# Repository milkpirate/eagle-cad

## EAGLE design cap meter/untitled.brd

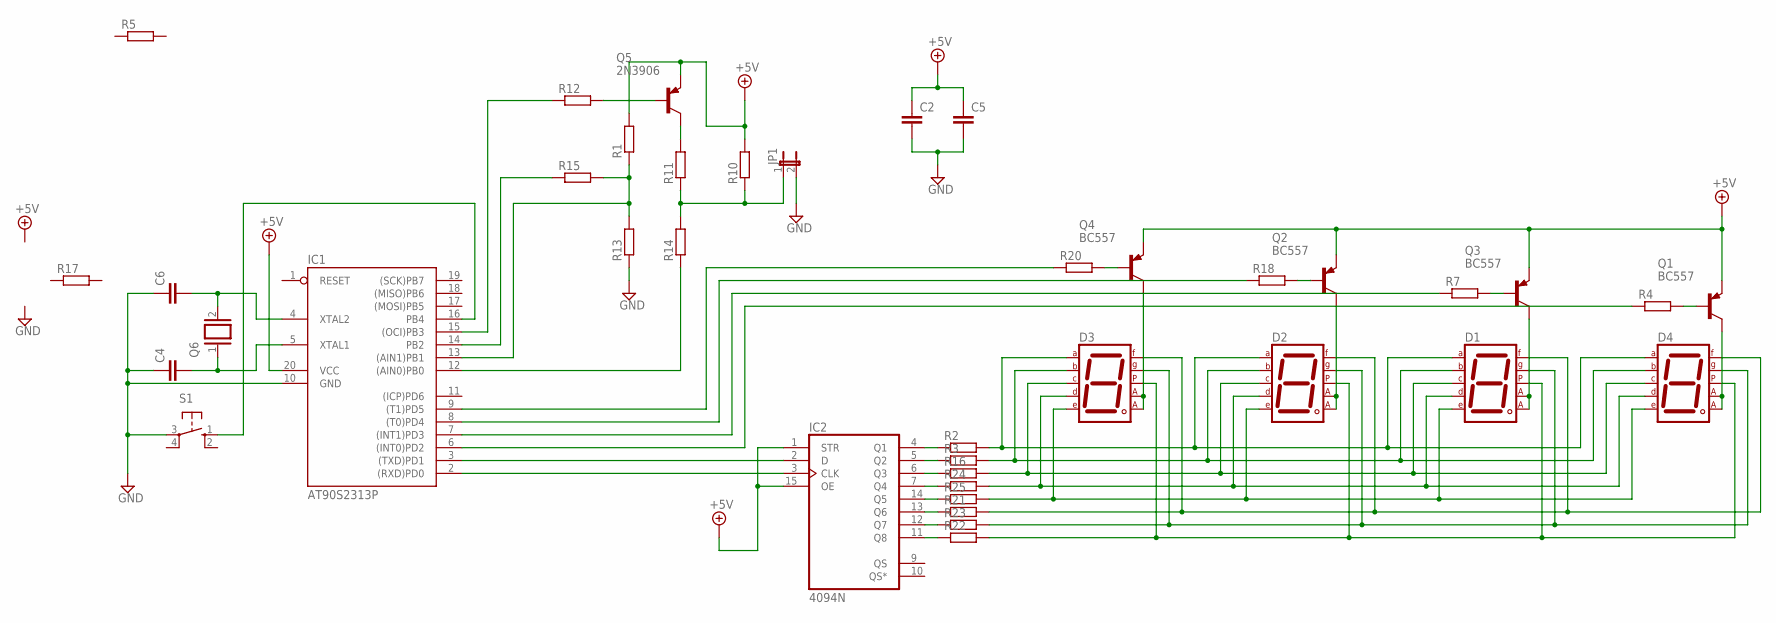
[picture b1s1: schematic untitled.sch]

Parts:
C2, C4, C5, C6: C-EU025-025X050; C025-025X050
D1, D2, D3, D4: 7SEG-CA; 7SEG-13
IC1: AT90S2313P; DIL20
IC2: 4094N; DIL16
JP1: JP1E; JP1
Q1, Q2, Q3, Q4: BC557; TO92
Q5: 2N3906; TO92
Q6: XTAL/S; QS
R1, R5, R10, R11, R12, R13, R14, R15, R17: R-EU_0204/2V; 0204V
R2, R3, R4, R7, R16, R18, R20, R22, R24, R25: R-EU_0204/7; 0204/7
R21, R23: R-EU_0207/12; 0207/12
S1: 10-XX; B3F-10XX

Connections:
+5V: C2.1, C5.1, IC1.20 (VCC), IC2.1 (STR), IC2.15 (OE), Q1.1 (E), Q2.1 (E), Q3.1 (E), Q4.1 (E), Q5.3 (E), R1.2, R10.2
GND: C2.2, C4.1, C5.2, C6.1, IC1.10 (GND), JP1.2, R13.1, S1.3
unnamed: Q1.2 (B), R4.2
unnamed: C4.2, IC1.5 (XTAL1), Q6.1
unnamed: C6.2, IC1.4 (XTAL2), Q6.2
unnamed: IC1.16 (PB4), S1.1 (S)
unnamed: Q5.1 (C), R11.2
unnamed: JP1.1, R10.1, R11.1, R14.2
unnamed: IC1.13 ((AIN1)PB1), R1.1, R13.2, R15.2
unnamed: Q5.2 (B), R12.2
unnamed: IC1.15 ((OCI)PB3), R12.1
unnamed: IC1.14 (PB2), R15.1
unnamed: IC1.12 ((AIN0)PB0), R14.1
unnamed: IC1.3 ((TXD)PD1), IC2.2 (D)
unnamed: IC1.2 ((RXD)PD0), IC2.3 (CLK)
unnamed: D1.9 (F), D2.9 (F), D3.9 (F), D4.9 (F), R21.2
unnamed: IC2.4 (Q1), R2.1
unnamed: IC2.5 (Q2), R3.1
unnamed: IC2.6 (Q3), R16.1
unnamed: IC2.7 (Q4), R24.1
unnamed: IC2.14 (Q5), R25.1
unnamed: IC2.13 (Q6), R21.1
unnamed: IC2.12 (Q7), R23.1
unnamed: IC2.11 (Q8), R22.1
unnamed: D1.7 (A), D2.7 (A), D3.7 (A), D4.7 (A), R2.2
unnamed: D1.6 (B), D2.6 (B), D3.6 (B), D4.6 (B), R3.2
unnamed: D1.4 (C), D2.4 (C), D3.4 (C), D4.4 (C), R16.2
unnamed: D1.2 (D), D2.2 (D), D3.2 (D), D4.2 (D), R24.2
unnamed: D1.1 (E), D2.1 (E), D3.1 (E), D4.1 (E), R25.2
unnamed: D1.10 (G), D2.10 (G), D3.10 (G), D4.10 (G), R23.2
unnamed: D1.5 (DP), D2.5 (DP), D3.5 (DP), D4.5 (DP), R22.2
unnamed: D1.3 (CA1), D1.8 (CA2), Q3.3 (C)
unnamed: D2.3 (CA1), D2.8 (CA2), Q2.3 (C)
unnamed: D3.3 (CA1), D3.8 (CA2), Q4.3 (C)
unnamed: D4.3 (CA1), D4.8 (CA2), Q1.3 (C)
unnamed: Q3.2 (B), R7.2
unnamed: Q2.2 (B), R18.2
unnamed: Q4.2 (B), R20.2
unnamed: IC1.6 ((INT0)PD2), R4.1
unnamed: IC1.7 ((INT1)PD3), R7.1
unnamed: IC1.8 ((T0)PD4), R18.1
unnamed: IC1.9 ((T1)PD5), R20.1
VDD: IC2.16 (VDD)
VSS: IC2.8 (VSS)

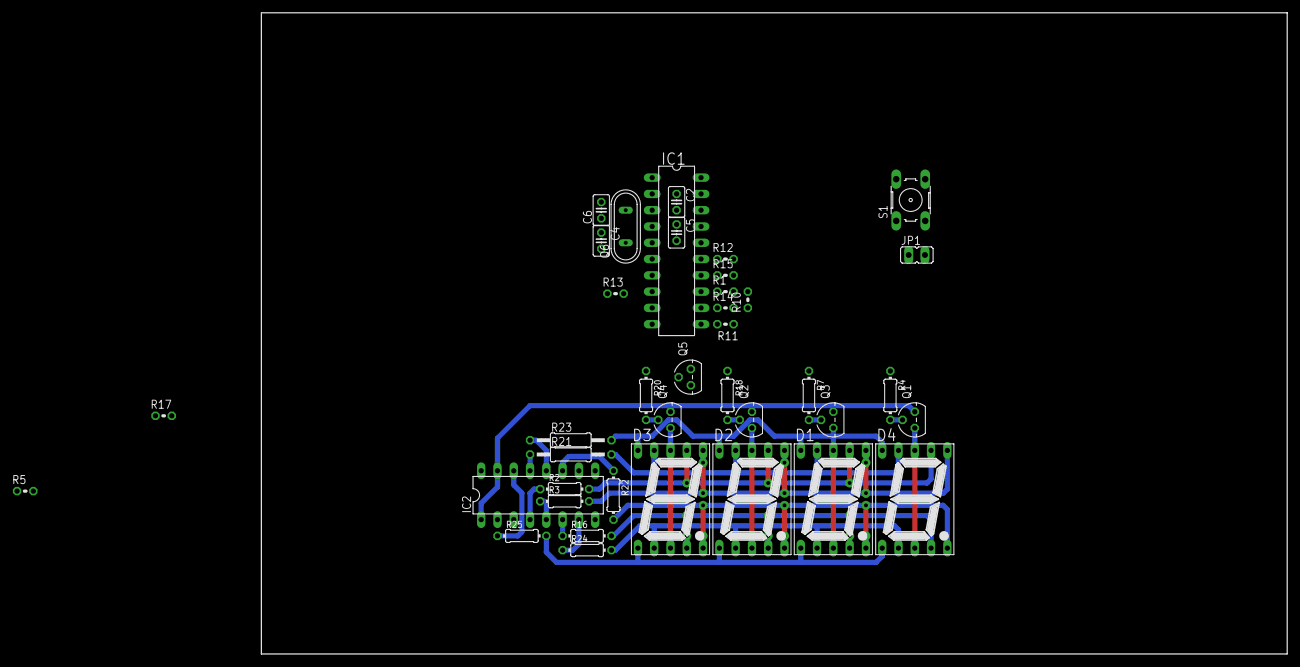
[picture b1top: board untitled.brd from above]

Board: 2 copper layers, 160.0 x 100.0 mm, 39 parts (0 on the bottom side), 42 nets.

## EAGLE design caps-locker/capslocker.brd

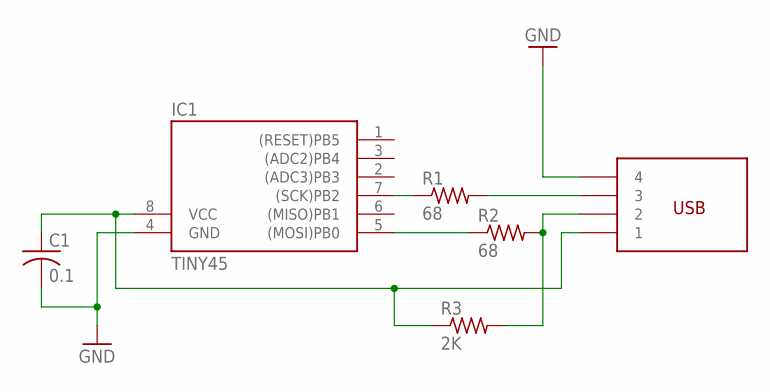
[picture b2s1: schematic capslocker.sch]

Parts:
C1: 0.1; C0805
IC1: TINY45; SOIC8
R1, R2: 68; R0603
R3: 2K; R0603
U$1: USB_A_EDGE

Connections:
GND: C1.2, IC1.4 (GND), U$1.P$3 (4)
unnamed: C1.1, IC1.8 (VCC), R3.1, U$1.P$4 (1)
unnamed: R1.2, U$1.P$1 (3)
unnamed: R2.2, R3.2, U$1.P$2 (2)
unnamed: IC1.7 ((SCK)PB2), R1.1
unnamed: IC1.5 ((MOSI)PB0), R2.1

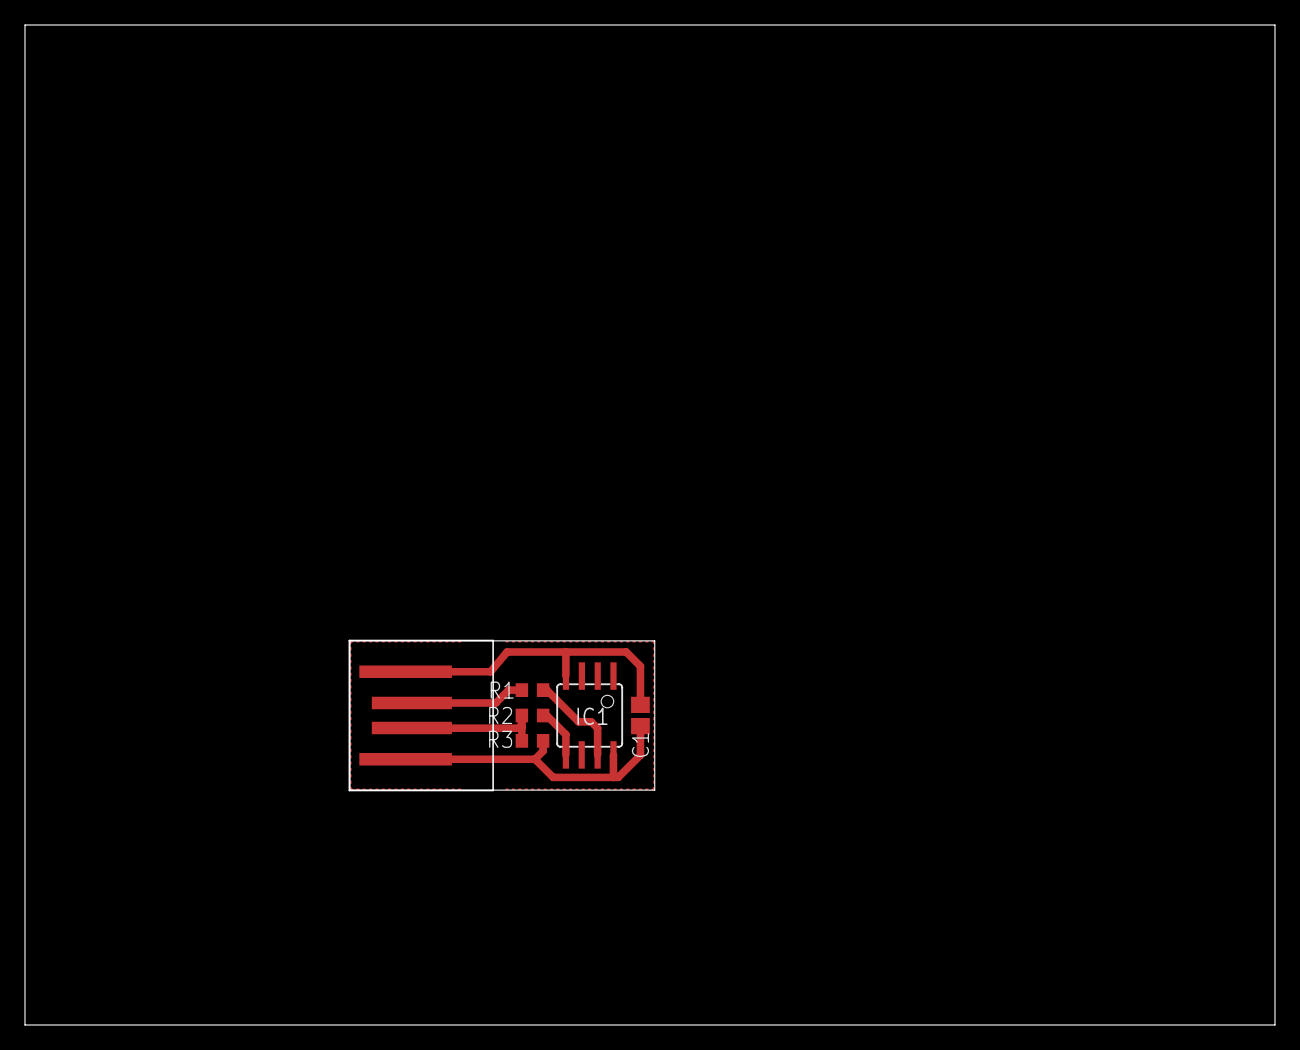
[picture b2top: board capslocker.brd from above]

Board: 2 copper layers, 100.0 x 80.0 mm, 6 parts (0 on the bottom side), 6 nets.

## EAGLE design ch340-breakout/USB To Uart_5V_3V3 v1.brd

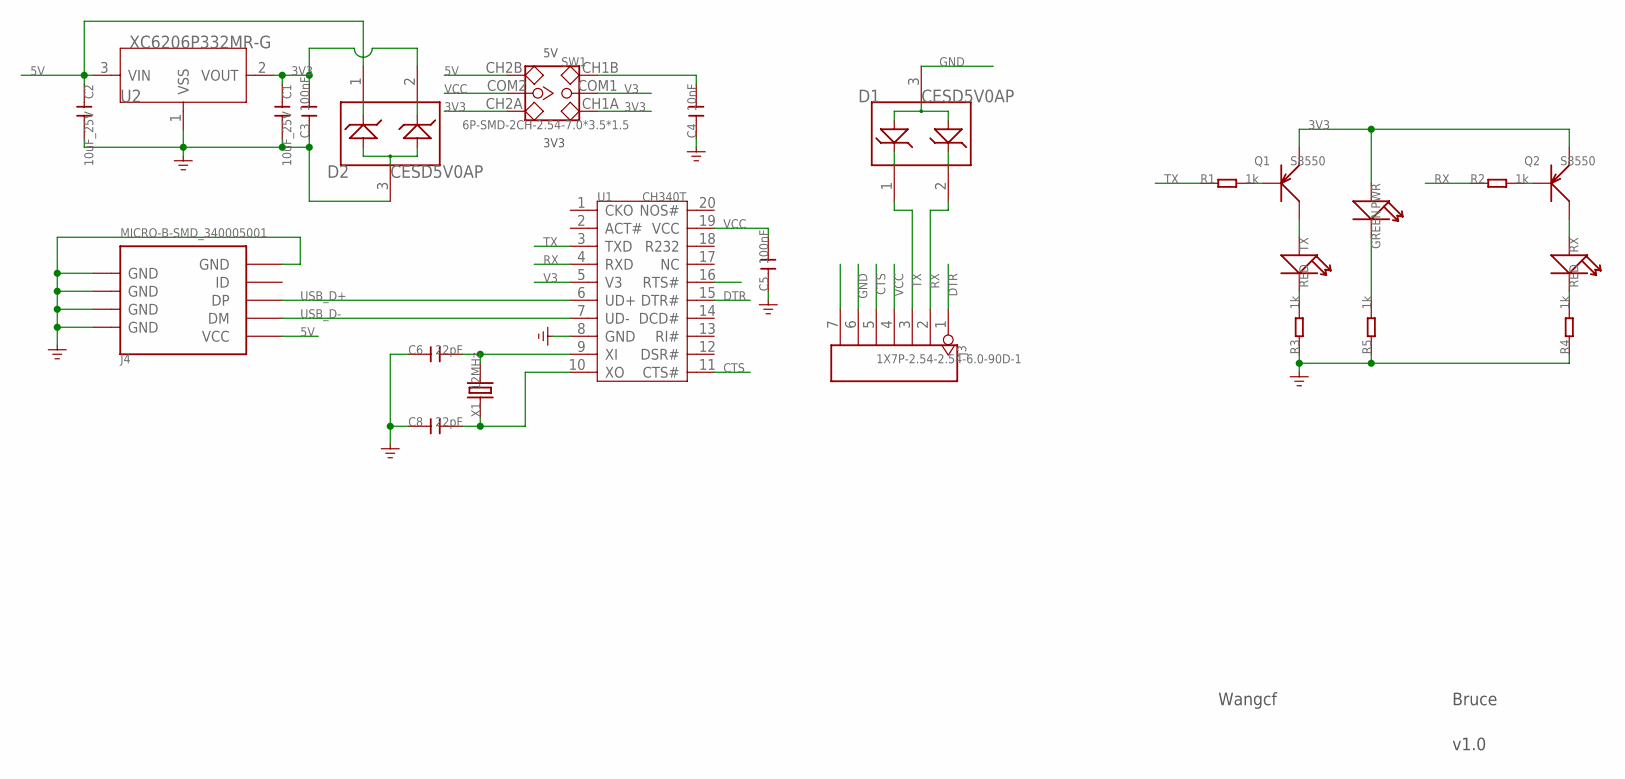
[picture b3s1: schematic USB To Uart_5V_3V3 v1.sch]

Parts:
C1, C2: 10uF_25V; C0805
C3, C5: 100nF; C0402
C4: 10nF; C0402
C6, C8: 22pF; C0402
D1, D2: CESD5V0AP; SOT23
J3: 1X7P-2.54-2.54-6.0-90D-1; 7P-2.54-65/35MIL
J4: MICRO-B-SMD_340005001; MICRO-USB
PWR: GREEN; LED-0603
Q1, Q2: S8550; SOT23
R1, R2, R3, R4, R5: 1k; R0402
RX: RED; LED-0603
SW1: 6P-SMD-2CH-2.54-7.0*3.5*1.5; 6P-SMD-2CH-2.54-3.5X7.2
TX: RED; LED-0603
U1: CH340T; SSOP20
U2: XC6206P332MR-G; SOT23
X1: 12MHz; 2P-SMD-5X3.2

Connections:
3V3: C1.1, C3.2, D2.2, PWR.+, Q1.2 (E), Q2.2 (E), SW1.CH1A, SW1.CH2A, U2.2 (VOUT)
5V: C2.1, D2.1, J4.1 (VCC), SW1.CH2B, U2.3 (VIN)
CTS: J3.5, U1.11 (CTS#)
DTR: J3.1, U1.15 (DTR#)
GND: C1.2, C2.2, C3.1, C4.1, C5.1, C6.1, C8.1, D1.3, D2.3, J3.6, J4.5 (GND), J4.S1 (GND), J4.S2 (GND), J4.S3 (GND), J4.S4 (GND), J4.S5 (GND), J4.S6 (GND), R3.1, R4.1, R5.1, U1.8 (GND), U2.1 (VSS)
unnamed: Q1.3 (C), TX.+
unnamed: Q2.3 (C), RX.+
unnamed: J3.7, U1.16 (RTS#)
unnamed: C6.2, U1.9 (XI), X1.2
unnamed: C8.2, U1.10 (XO), X1.1
unnamed: R3.2, TX.-
unnamed: Q1.1 (B), R1.2
unnamed: Q2.1 (B), R2.2
unnamed: C4.2, SW1.CH1B
unnamed: R4.2, RX.-
unnamed: PWR.-, R5.2
RX: D1.2, J3.2, R2.1, U1.4 (RXD)
TX: D1.1, J3.3, R1.1, U1.3 (TXD)
USB_D+: J4.3 (DP), U1.6 (UD+)
USB_D-: J4.2 (DM), U1.7 (UD-)
V3: SW1.COM1, U1.5 (V3)
VCC: C5.2, J3.4, SW1.COM2, U1.19 (VCC)

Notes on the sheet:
3V3
Wangcf
Bruce
v1.0

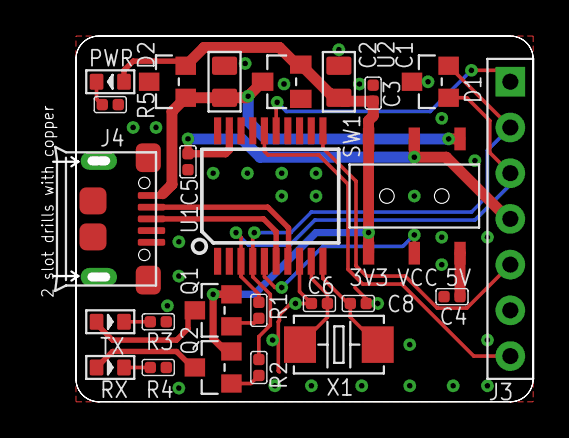
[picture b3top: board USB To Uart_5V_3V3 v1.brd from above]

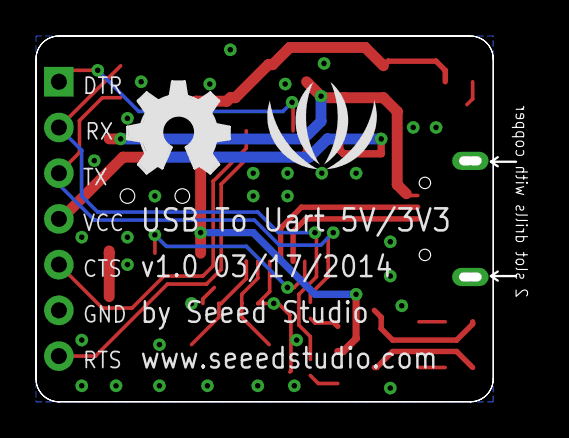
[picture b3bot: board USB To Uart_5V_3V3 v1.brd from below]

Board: 2 copper layers, 26.7 x 20.3 mm, 27 parts (2 on the bottom side), 22 nets.

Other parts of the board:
U$8: LOGO_SILK
U$9: OSHW_FILLX200_NOTEXT

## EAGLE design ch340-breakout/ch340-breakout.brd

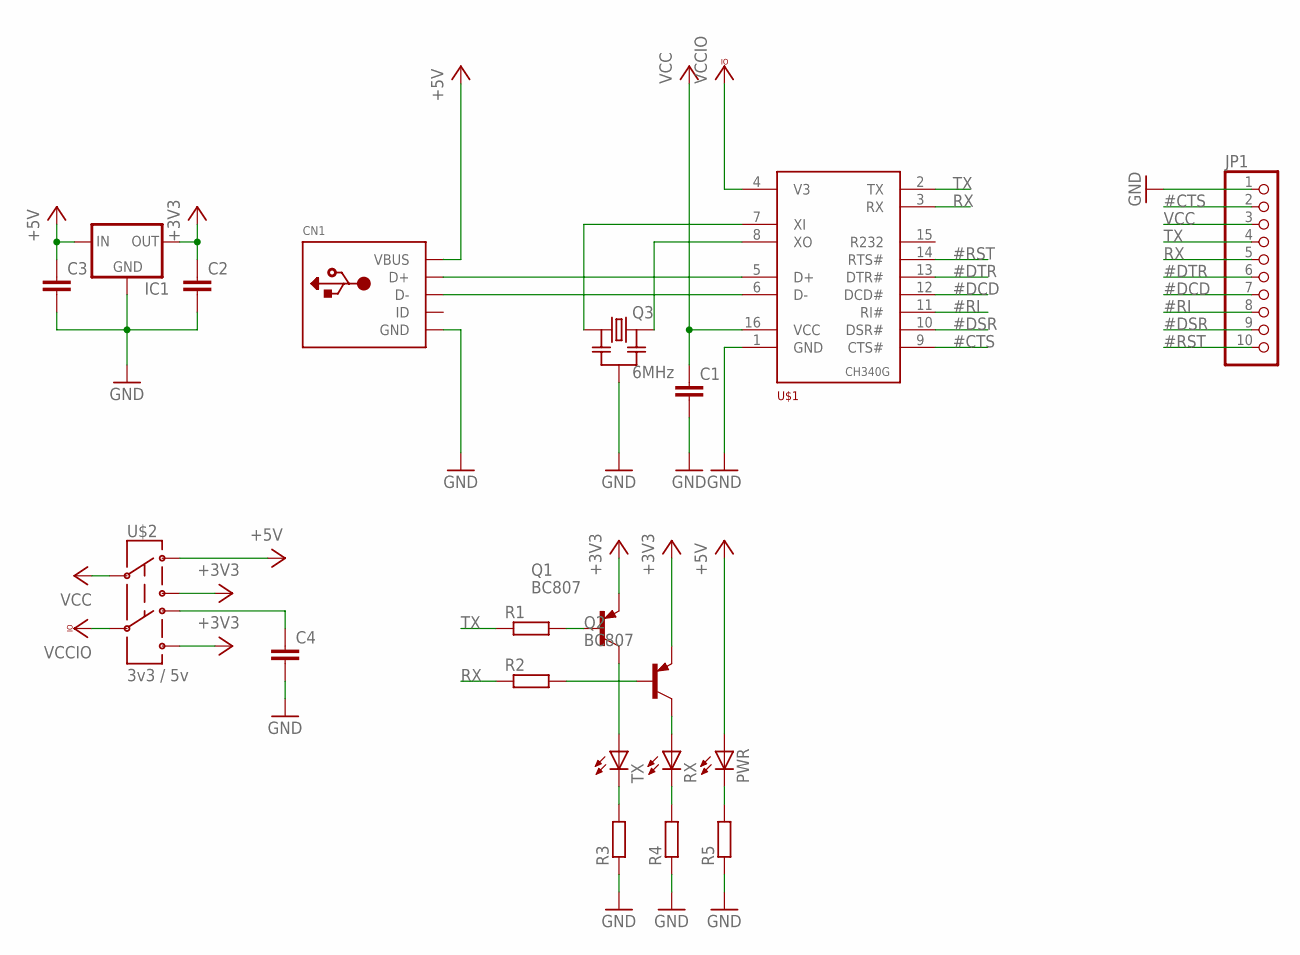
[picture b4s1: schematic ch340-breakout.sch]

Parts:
C1, C2, C3, C4: C-EUC0805; C0805
CN1: USBTHM; USB-MINIB-THM
IC1: MCP1700_SOT-32; SOT23
JP1: PINHD-1X10; 1X10
PWR: LEDSML0805; SML0805
Q1, Q2: BC807; SOT23-BEC
Q3: 6MHz; RESONATOR_MURATA3
R1, R2, R3, R4, R5: R-EU_R0805; R0805
RX: LEDSML0805; SML0805
TX: LEDSML0805; SML0805
U$1: CH340G; SO16
U$2: 3v3 / 5v; AYZ0202

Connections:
#CTS: JP1.2, U$1.9 (CTS#)
#DCD: JP1.7, U$1.12 (DCD#)
#DSR: JP1.9, U$1.10 (DSR#)
#DTR: JP1.6, U$1.13 (DTR#)
#RI: JP1.8, U$1.11 (RI#)
#RST: JP1.10, U$1.14 (RTS#)
+3V3: C2.1, IC1.2 (OUT), Q1.E, Q2.E, U$2.1 (3), U$2.4 (6)
+5V: C3.1, CN1.VBUS, IC1.3 (IN), PWR.A, U$2.3 (1)
GND: C1.2, C2.2, C3.2, C4.2, CN1.GND, IC1.1 (GND), JP1.1, Q3.2, R3.1, R4.1, R5.1, U$1.1 (GND)
unnamed: CN1.D+, U$1.5 (D+)
unnamed: CN1.D-, U$1.6 (D-)
unnamed: Q3.1, U$1.7 (XI)
unnamed: Q3.3, U$1.8 (XO)
unnamed: C4.1, U$2.6 (4)
unnamed: PWR.C, R5.2
unnamed: R3.2, TX.C
unnamed: R4.2, RX.C
unnamed: Q2.C, RX.A
unnamed: Q1.C, TX.A
unnamed: Q2.B, R2.2
unnamed: Q1.B, R1.2
RX: JP1.5, R2.1, U$1.3 (RX)
TX: JP1.4, R1.1, U$1.2 (TX)
VCC: C1.1, JP1.3, U$1.16 (VCC), U$2.2
VCCIO: U$1.4 (V3), U$2.5

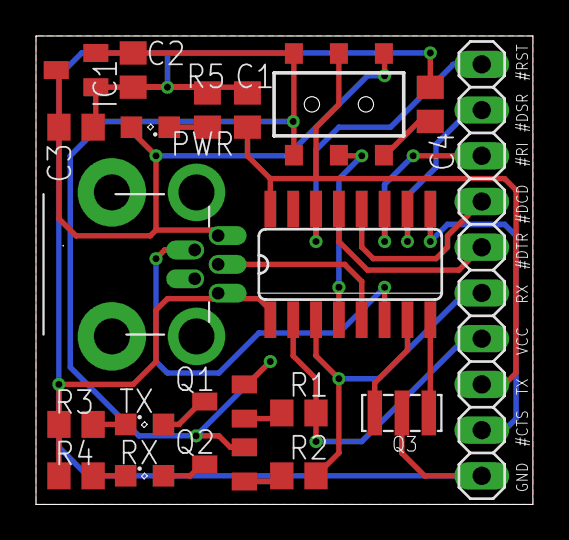
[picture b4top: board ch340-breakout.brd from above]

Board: 2 copper layers, 27.6 x 26.0 mm, 20 parts (0 on the bottom side), 25 nets.

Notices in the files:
parts and their libraries:
m-pad-2.1: License : GNU General Public License version 2 (see bottom)
SparkFun-Electromechanical: Licensing: Creative Commons ShareAlike 4.0 International - https://creativecommons.org/licenses/by-sa/4.0
